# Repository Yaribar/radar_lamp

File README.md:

# Radar Lamp

ESP32-C3 Super Mini project that dims a lamp based on distance measured by an Acconeer XE121 radar sensor (A121 chip).

## Hardware

- **MCU**: ESP32-C3 Super Mini
- **Sensor**: Acconeer XE121 (A121 radar)

## Wiring

| Signal    | ESP32-C3 GPIO |
|-----------|--------------|
| ENABLE    | 3            |
| INTERRUPT | 5            |
| SCLK      | 6            |
| MOSI      | 7            |
| MISO      | 2            |
| CS        | 10           |
| SEL0      | 1            |
| SEL1      | 0            |
| SEL2      | 4            |
| LED       | 8 (built-in) |

> **Note:** GPIO 9 (BOOT), 8 (LED), and 18/19 (USB) were intentionally avoided for sensor SEL pins.

## Build

Requires ESP-IDF 6.1.

```bash
# 1. Source IDF (required every new terminal session)
. ~/esp/esp-idf/export.sh

# 2. Go to project
cd ~/esp/radar_lamp

# 3. Set target (only needed once or after cleaning)
idf.py set-target esp32c3

# 4. Build
idf.py build

# 5. Find your port
ls /dev/cu.*

# 6. Flash and open monitor
idf.py -p /dev/cu.YOURPORT flash monitor
```

> To exit the monitor press **Ctrl + ]**

## How it works

### Distance → brightness mapping

| Distance | Brightness |
|----------|-----------|
| ≤ 0.5 m  | 100%      |
| 1.15 m   | ~50%      |
| ≥ 1.8 m  | 0%        |

When multiple distances are detected (e.g. paper lamp shade + person), the furthest reading is always used. The sensor start range is set to 0.30 m to exclude the paper shade (~10 cm away).

### Perceptual brightness (gamma correction)

A raw linear PWM sweep from 0→100% does not look linear to the human eye — it appears to jump quickly at low values and barely change at high values. This is because **eyes perceive brightness logarithmically**.

To fix this, a gamma curve (`γ = 2.2`) is applied to the PWM duty cycle:

```
PWM duty = (brightness%)^2.2
```

This makes the lamp appear to change evenly as you move toward or away from it.

### LED state machine

```
valid reading               valid reading
      │                           │
 ┌────▼──────┐  no reading   ┌────▼─────┐
 │ TRACKING  │ ────────────► │ HOLDING  │
 │           │ ◄──────────── │          │
 └───────────┘  reading back └────┬─────┘
                                  │ 3 s timeout
                                  ▼
                            ┌──────────┐
                            │  FADING  │ → slowly → 0%
                            └──────────┘
```

- **TRACKING**: smoothly follows distance (max 2%/50 ms tick ≈ 2.5 s full sweep)
- **HOLDING**: no reading detected, holds current brightness for 3 s
- **FADING**: slowly fades to off (0.5%/tick ≈ 16 s full sweep)

### Key hardware notes

- SPI speed is **10 MHz** — 40 MHz causes calibration failures over breadboard wires
- Sensor range: **0.30 m to 3.0 m** (balanced preset)

## PCB / Hardware design

### Circuit overview

12V barrel jack → Mini 360 step-down → 3.3V for ESP32 + XE121
12V barrel jack → IRLZ44N MOSFET (controlled by GPIO 8 PWM) → 12V LED lamp

### BOM

| Component | Value | Purpose |
|---|---|---|
| ESP32-C3 Super Mini | — | MCU |
| XE121 radar | — | distance sensor |
| IRLZ44N | — | MOSFET, switches 12V lamp via PWM |
| Mini 360 MP2307 | 12V → 3.3V | power regulation |
| Resistor | 100Ω | MOSFET gate series — limits inrush, prevents oscillation |
| Resistor | 10kΩ | MOSFET gate pull-down — keeps lamp off when GPIO floats on boot |
| Capacitor | 100nF ceramic | near ESP32 3.3V pin — absorbs high-freq switching noise |
| Barrel jack | 5.5/2.1mm | 12V input |
| Connector | SH1.0mm 8-pin vertical | XE121 radar |
| Connector | XH2.54 2-pin | 12V lamp output |
| Switch | SPST | power on/off |

### Notes
- No flyback diode needed — lamp is a resistive LED load, no inductive spike
- No fuse on board — power supply has built-in protection
- 100µF on 12V input not needed — Mini 360 + regulated PSU covers it
- IRLZ44N is rated 47A/55V, far above what a 12V LED lamp needs — chosen for logic-level gate compatibility with 3.3V GPIO
- Lamp connector XH2.54 is rated for up to ~3A — verify lamp wattage stays within that (W/12V < 3A, so under 36W)

## License

Acconeer source files are licensed under BSD 3-Clause. See [LICENSES/license_acconeer.txt](LICENSES/license_acconeer.txt).

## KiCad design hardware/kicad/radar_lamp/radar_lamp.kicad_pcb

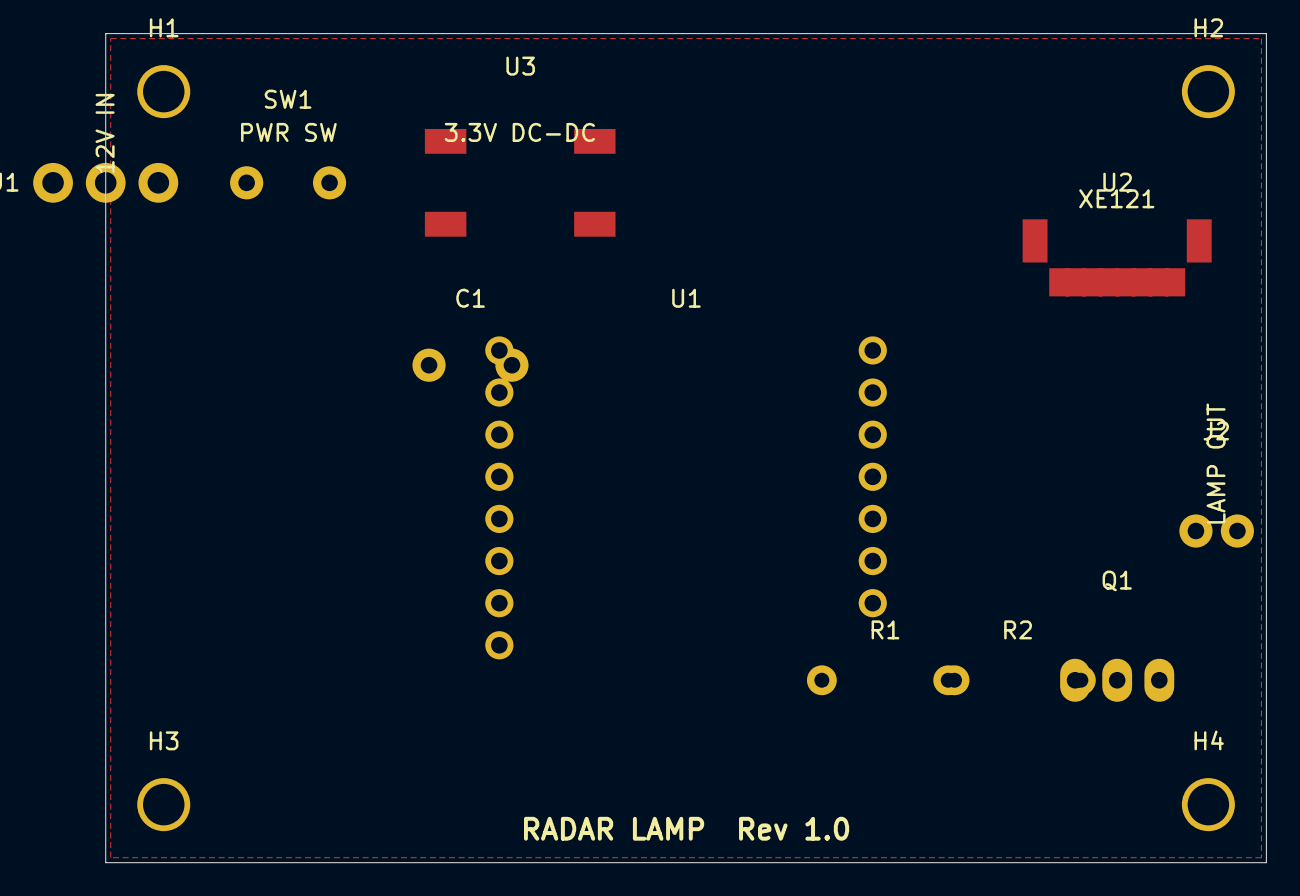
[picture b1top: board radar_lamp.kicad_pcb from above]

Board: 2 copper layers, 70.0 x 50.0 mm, 14 parts (0 on the bottom side), 11 nets, no tracks yet.

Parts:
C1: 100nF; C_Disc_D5.0mm_W2.5mm_P5.00mm
H1, H2, H3, H4: MountingHole_2.5mm
J1: Barrel_Jack_5.5/2.1mm; BarrelJack_Horizontal_54-00166
J2: LED_Lamp_12V; JST_XH_B2B-XH-A_1x02_P2.50mm_Vertical
Q1: IRLZ44N; TO-220-3_Vertical
R1: 100R; R_Axial_DIN0207_L6.3mm_D2.5mm_P7.62mm_Horizontal
R2: 10k; R_Axial_DIN0207_L6.3mm_D2.5mm_P7.62mm_Horizontal
SW1: SW_SPST; SW_Slide_1P2T_CK_OS102011MS2QN1
U1: ESP32-C3-SuperMini
U2: Acconeer_XE121; JST_SH_SM08B-SRSS-TB_1x08-1MP_P1mm_Horizontal
U3: Mini360_3V3; Mini360

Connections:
+3V3: C1.1, U1.1, U2.1, U3.3
+12V: J1.1, SW1.1
+12V_SWITCHED: J2.1, SW1.2, U3.1
GND: C1.2, J1.2, Q1.3, R2.2, U1.2, U1.14, U2.2, U3.2, U3.4
LED_PWM: R1.1, U1.7
RADAR_EN: U1.13, U2.7
RADAR_INT: U1.4, U2.8
SPI_CS: U1.8, U2.6
SPI_MISO: U1.12, U2.4
SPI_MOSI: U1.6, U2.3
SPI_SCLK: U1.5, U2.5
